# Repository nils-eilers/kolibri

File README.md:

kolibri
=======

About
-----

kolibri is an 8 bit homebrew computer project, based on the 6309 CPU by
Hitachi, a kind of advanced edition of the much more famous CPU 6809 by
Motorola.

kolibri is the german word for colibri aka hummingbird.

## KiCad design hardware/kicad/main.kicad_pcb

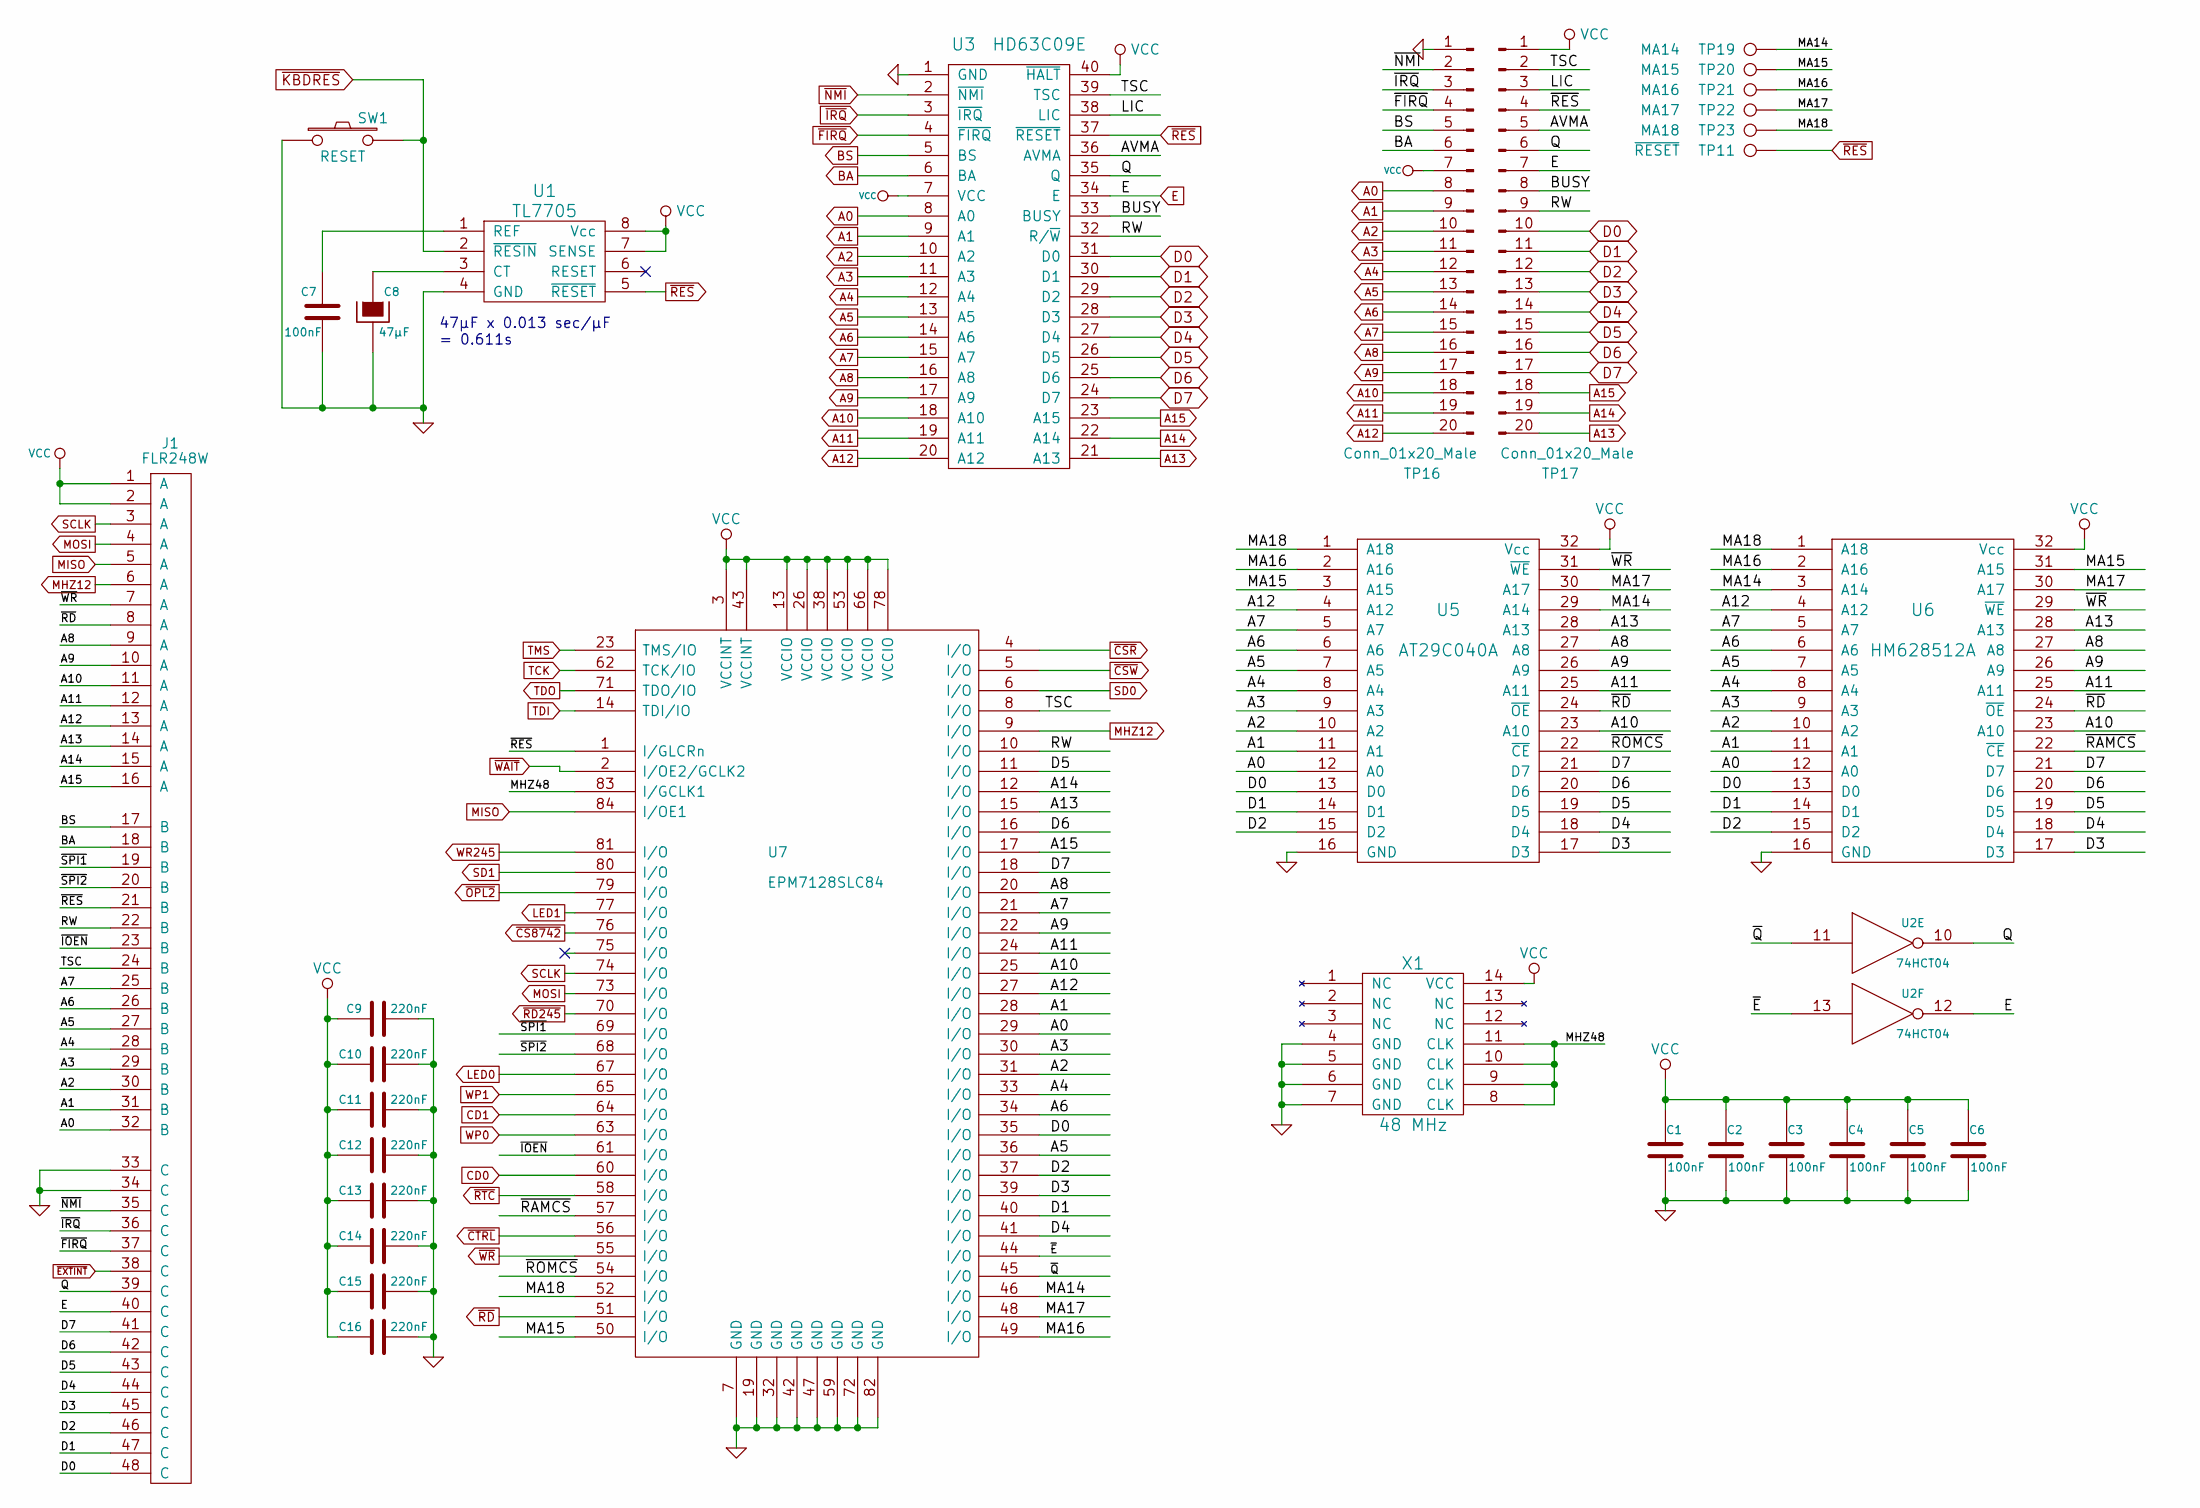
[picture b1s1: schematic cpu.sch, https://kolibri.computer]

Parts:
C1, C2, C3, C4, C5, C6, C7: 100nF; KERKO-5
C8: 47µF; CP-2-5
C9, C10, C11, C12, C13, C14, C15, C16: 220nF; KERKO-5
J1: FLR248W; FL-R2-48W
SW1: RESET; TASTER_3305
TP11: ~RESET; PINTST
TP16, TP17: Conn_01x20_Male; Pin_Header_Straight_1x20_Pitch2.54mm
TP19: MA14; PINTST
TP20: MA15; PINTST
TP21: MA16; PINTST
TP22: MA17; PINTST
TP23: MA18; PINTST
U1: TL7705; DIP-8
U2: 74HCT04; DIP-14
U3: HD63C09E; DIP-40
U5: AT29C040A; DIP-32
U6: HM628512A; DIP-32
U7: EPM7128SLC84; PLCC-84
X1: 48 MHz; OSC

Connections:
/CPU/AVMA: TP17.5, U3.36 (AVMA)
/CPU/BUSY: TP17.8, U3.33 (BUSY)
/CPU/LIC: TP17.3, U3.38 (LIC)
/CPU/MA14: TP19.1, U5.29 (A14), U6.3 (A14), U7.46 (I/O)
/CPU/MA15: TP20.1, U5.3 (A15), U6.31 (A15), U7.50 (I/O)
/CPU/MA16: TP21.1, U5.2 (A16), U6.2 (A16), U7.49 (I/O)
/CPU/MA17: TP22.1, U5.30 (A17), U6.30 (A17), U7.48 (I/O)
/CPU/MA18: TP23.1, U5.1 (A18), U6.1 (A18), U7.52 (I/O)
/CPU/MHZ48: U7.83 (I/GCLK1), X1.8 (CLK), X1.9 (CLK), X1.10 (CLK), X1.11 (CLK)
/CPU/Q: J1.39 (C), TP17.6, U2.10, U3.35 (Q)
/CPU/RW: J1.22 (B), TP17.9, U3.32 (R/~W), U7.10 (I/O)
/CPU/TSC: J1.24 (B), TP17.2, U3.39 (TSC), U7.8 (I/O)
/CPU/~E: U2.13, U7.44 (I/O)
/CPU/~IOEN: J1.23 (B), U7.61 (I/O)
/CPU/~Q: U2.11, U7.45 (I/O)
/CPU/~RAMCS: U6.22 (~CE), U7.57 (I/O)
/CPU/~ROMCS: U5.22 (~CE), U7.54 (I/O)
/CPU/~SPI1: J1.19 (B), U7.69 (I/O)
/CPU/~SPI2: J1.20 (B), U7.68 (I/O)
A0: J1.32 (B), TP16.8, U3.8 (A0), U5.12 (A0), U6.12 (A0), U7.29 (I/O); also elsewhere on the board
A1: J1.31 (B), TP16.9, U3.9 (A1), U5.11 (A1), U6.11 (A1), U7.28 (I/O); also elsewhere on the board
A2: J1.30 (B), TP16.10, U3.10 (A2), U5.10 (A2), U6.10 (A2), U7.31 (I/O); also elsewhere on the board
A3: J1.29 (B), TP16.11, U3.11 (A3), U5.9 (A3), U6.9 (A3), U7.30 (I/O); also elsewhere on the board
A4: J1.28 (B), TP16.12, U3.12 (A4), U5.8 (A4), U6.8 (A4), U7.33 (I/O)
A5: J1.27 (B), TP16.13, U3.13 (A5), U5.7 (A5), U6.7 (A5), U7.36 (I/O)
A6: J1.26 (B), TP16.14, U3.14 (A6), U5.6 (A6), U6.6 (A6), U7.34 (I/O)
A7: J1.25 (B), TP16.15, U3.15 (A7), U5.5 (A7), U6.5 (A7), U7.21 (I/O)
A8: J1.9 (A), TP16.16, U3.16 (A8), U5.27 (A8), U6.27 (A8), U7.20 (I/O)
A9: J1.10 (A), TP16.17, U3.17 (A9), U5.26 (A9), U6.26 (A9), U7.22 (I/O)
A10: J1.11 (A), TP16.18, U3.18 (A10), U5.23 (A10), U6.23 (A10), U7.25 (I/O)
A11: J1.12 (A), TP16.19, U3.19 (A11), U5.25 (A11), U6.25 (A11), U7.24 (I/O)
A12: J1.13 (A), TP16.20, U3.20 (A12), U5.4 (A12), U6.4 (A12), U7.27 (I/O)
A13: J1.14 (A), TP17.20, U3.21 (A13), U5.28 (A13), U6.28 (A13), U7.15 (I/O)
A14: J1.15 (A), TP17.19, U3.22 (A14), U7.12 (I/O)
A15: J1.16 (A), TP17.18, U3.23 (A15), U7.17 (I/O)
BA: J1.18 (B), TP16.6, U3.6 (BA); also elsewhere on the board
BS: J1.17 (B), TP16.5, U3.5 (BS); also elsewhere on the board
CD0: U7.60 (I/O); also elsewhere on the board
CD1: U7.64 (I/O); also elsewhere on the board
D0: J1.48 (C), TP17.10, U3.31 (D0), U5.13 (D0), U6.13 (D0), U7.35 (I/O); also elsewhere on the board
D1: J1.47 (C), TP17.11, U3.30 (D1), U5.14 (D1), U6.14 (D1), U7.40 (I/O); also elsewhere on the board
D2: J1.46 (C), TP17.12, U3.29 (D2), U5.15 (D2), U6.15 (D2), U7.37 (I/O); also elsewhere on the board
D3: J1.45 (C), TP17.13, U3.28 (D3), U5.17 (D3), U6.17 (D3), U7.39 (I/O); also elsewhere on the board
D4: J1.44 (C), TP17.14, U3.27 (D4), U5.18 (D4), U6.18 (D4), U7.41 (I/O); also elsewhere on the board
D5: J1.43 (C), TP17.15, U3.26 (D5), U5.19 (D5), U6.19 (D5), U7.11 (I/O); also elsewhere on the board
D6: J1.42 (C), TP17.16, U3.25 (D6), U5.20 (D6), U6.20 (D6), U7.16 (I/O); also elsewhere on the board
D7: J1.41 (C), TP17.17, U3.24 (D7), U5.21 (D7), U6.21 (D7), U7.18 (I/O); also elsewhere on the board
E: J1.40 (C), TP17.7, U2.12, U3.34 (E); also elsewhere on the board
GND: C1.2, C2.2, C3.2, C4.2, C5.2, C6.2, C7.1, C8.2, C9.2, C10.2, C11.2, C12.2, C13.2, C14.2, C15.2, C16.2, J1.33 (C), J1.34 (C), SW1.1, TP16.1, U1.4 (GND), U2.7 (GND), U3.1 (GND), U5.16 (GND), U6.16 (GND), U7.7 (GND), U7.19 (GND), U7.32 (GND), U7.42 (GND), U7.47 (GND), U7.59 (GND), U7.72 (GND), U7.82 (GND), X1.4 (GND), X1.5 (GND), X1.6 (GND), X1.7 (GND); also elsewhere on the board
LED0: U7.67 (I/O); also elsewhere on the board
LED1: U7.77 (I/O); also elsewhere on the board
MHZ12: J1.6 (A), U7.9 (I/O); also elsewhere on the board
MISO: J1.5 (A), U7.84 (I/OE1); also elsewhere on the board
MOSI: J1.4 (A), U7.73 (I/O); also elsewhere on the board
unnamed: C7.2, U1.1 (REF)
unnamed: C8.1, U1.3 (CT)
SCLK: J1.3 (A), U7.74 (I/O); also elsewhere on the board
SD0: U7.6 (I/O); also elsewhere on the board
SD1: U7.80 (I/O); also elsewhere on the board
TCK: U7.62 (TCK/IO); also elsewhere on the board
TDI: U7.14 (TDI/IO); also elsewhere on the board
TDO: U7.71 (TDO/IO); also elsewhere on the board
TMS: U7.23 (TMS/IO); also elsewhere on the board
VCC: C1.1, C2.1, C3.1, C4.1, C5.1, C6.1, C9.1, C10.1, C11.1, C12.1, C13.1, C14.1, C15.1, C16.1, J1.1 (A), J1.2 (A), TP16.7, TP17.1, U1.7 (SENSE), U1.8 (Vcc), U2.14 (VCC), U3.7 (VCC), U3.40 (~HALT), U5.32 (Vcc), U6.32 (Vcc), U7.3 (VCCINT), U7.13 (VCCIO), U7.26 (VCCIO), U7.38 (VCCIO), U7.43 (VCCINT), U7.53 (VCCIO), U7.66 (VCCIO), U7.78 (VCCIO), X1.14 (VCC); also elsewhere on the board
WP0: U7.63 (I/O); also elsewhere on the board
WP1: U7.65 (I/O); also elsewhere on the board
WR245: U7.81 (I/O); also elsewhere on the board
~CS8742: U7.76 (I/O); also elsewhere on the board
~CSR: U7.4 (I/O); also elsewhere on the board
~CSW: U7.5 (I/O); also elsewhere on the board
~CTRL: U7.56 (I/O); also elsewhere on the board
~EXTINT: J1.38 (C); also elsewhere on the board
~FIRQ: J1.37 (C), TP16.4, U3.4 (~FIRQ); also elsewhere on the board
~IRQ: J1.36 (C), TP16.3, U3.3 (~IRQ); also elsewhere on the board
~KBDRES: SW1.2, U1.2 (~RESIN); also elsewhere on the board
~NMI: J1.35 (C), TP16.2, U3.2 (~NMI); also elsewhere on the board
~OPL2: U7.79 (I/O); also elsewhere on the board
~RD: J1.8 (A), U5.24 (~OE), U6.24 (~OE), U7.51 (I/O); also elsewhere on the board
~RD245: U7.70 (I/O); also elsewhere on the board
~RES: J1.21 (B), TP11.1, TP17.4, U1.5 (~RESET), U3.37 (~RESET), U7.1 (I/GLCRn); also elsewhere on the board
~RTC: U7.58 (I/O); also elsewhere on the board
~WAIT: U7.2 (I/OE2/GCLK2); also elsewhere on the board
~WR: J1.7 (A), U5.31 (~WE), U6.29 (~WE), U7.55 (I/O); also elsewhere on the board

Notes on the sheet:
47µF x 0.013 sec/µF = 0.611s

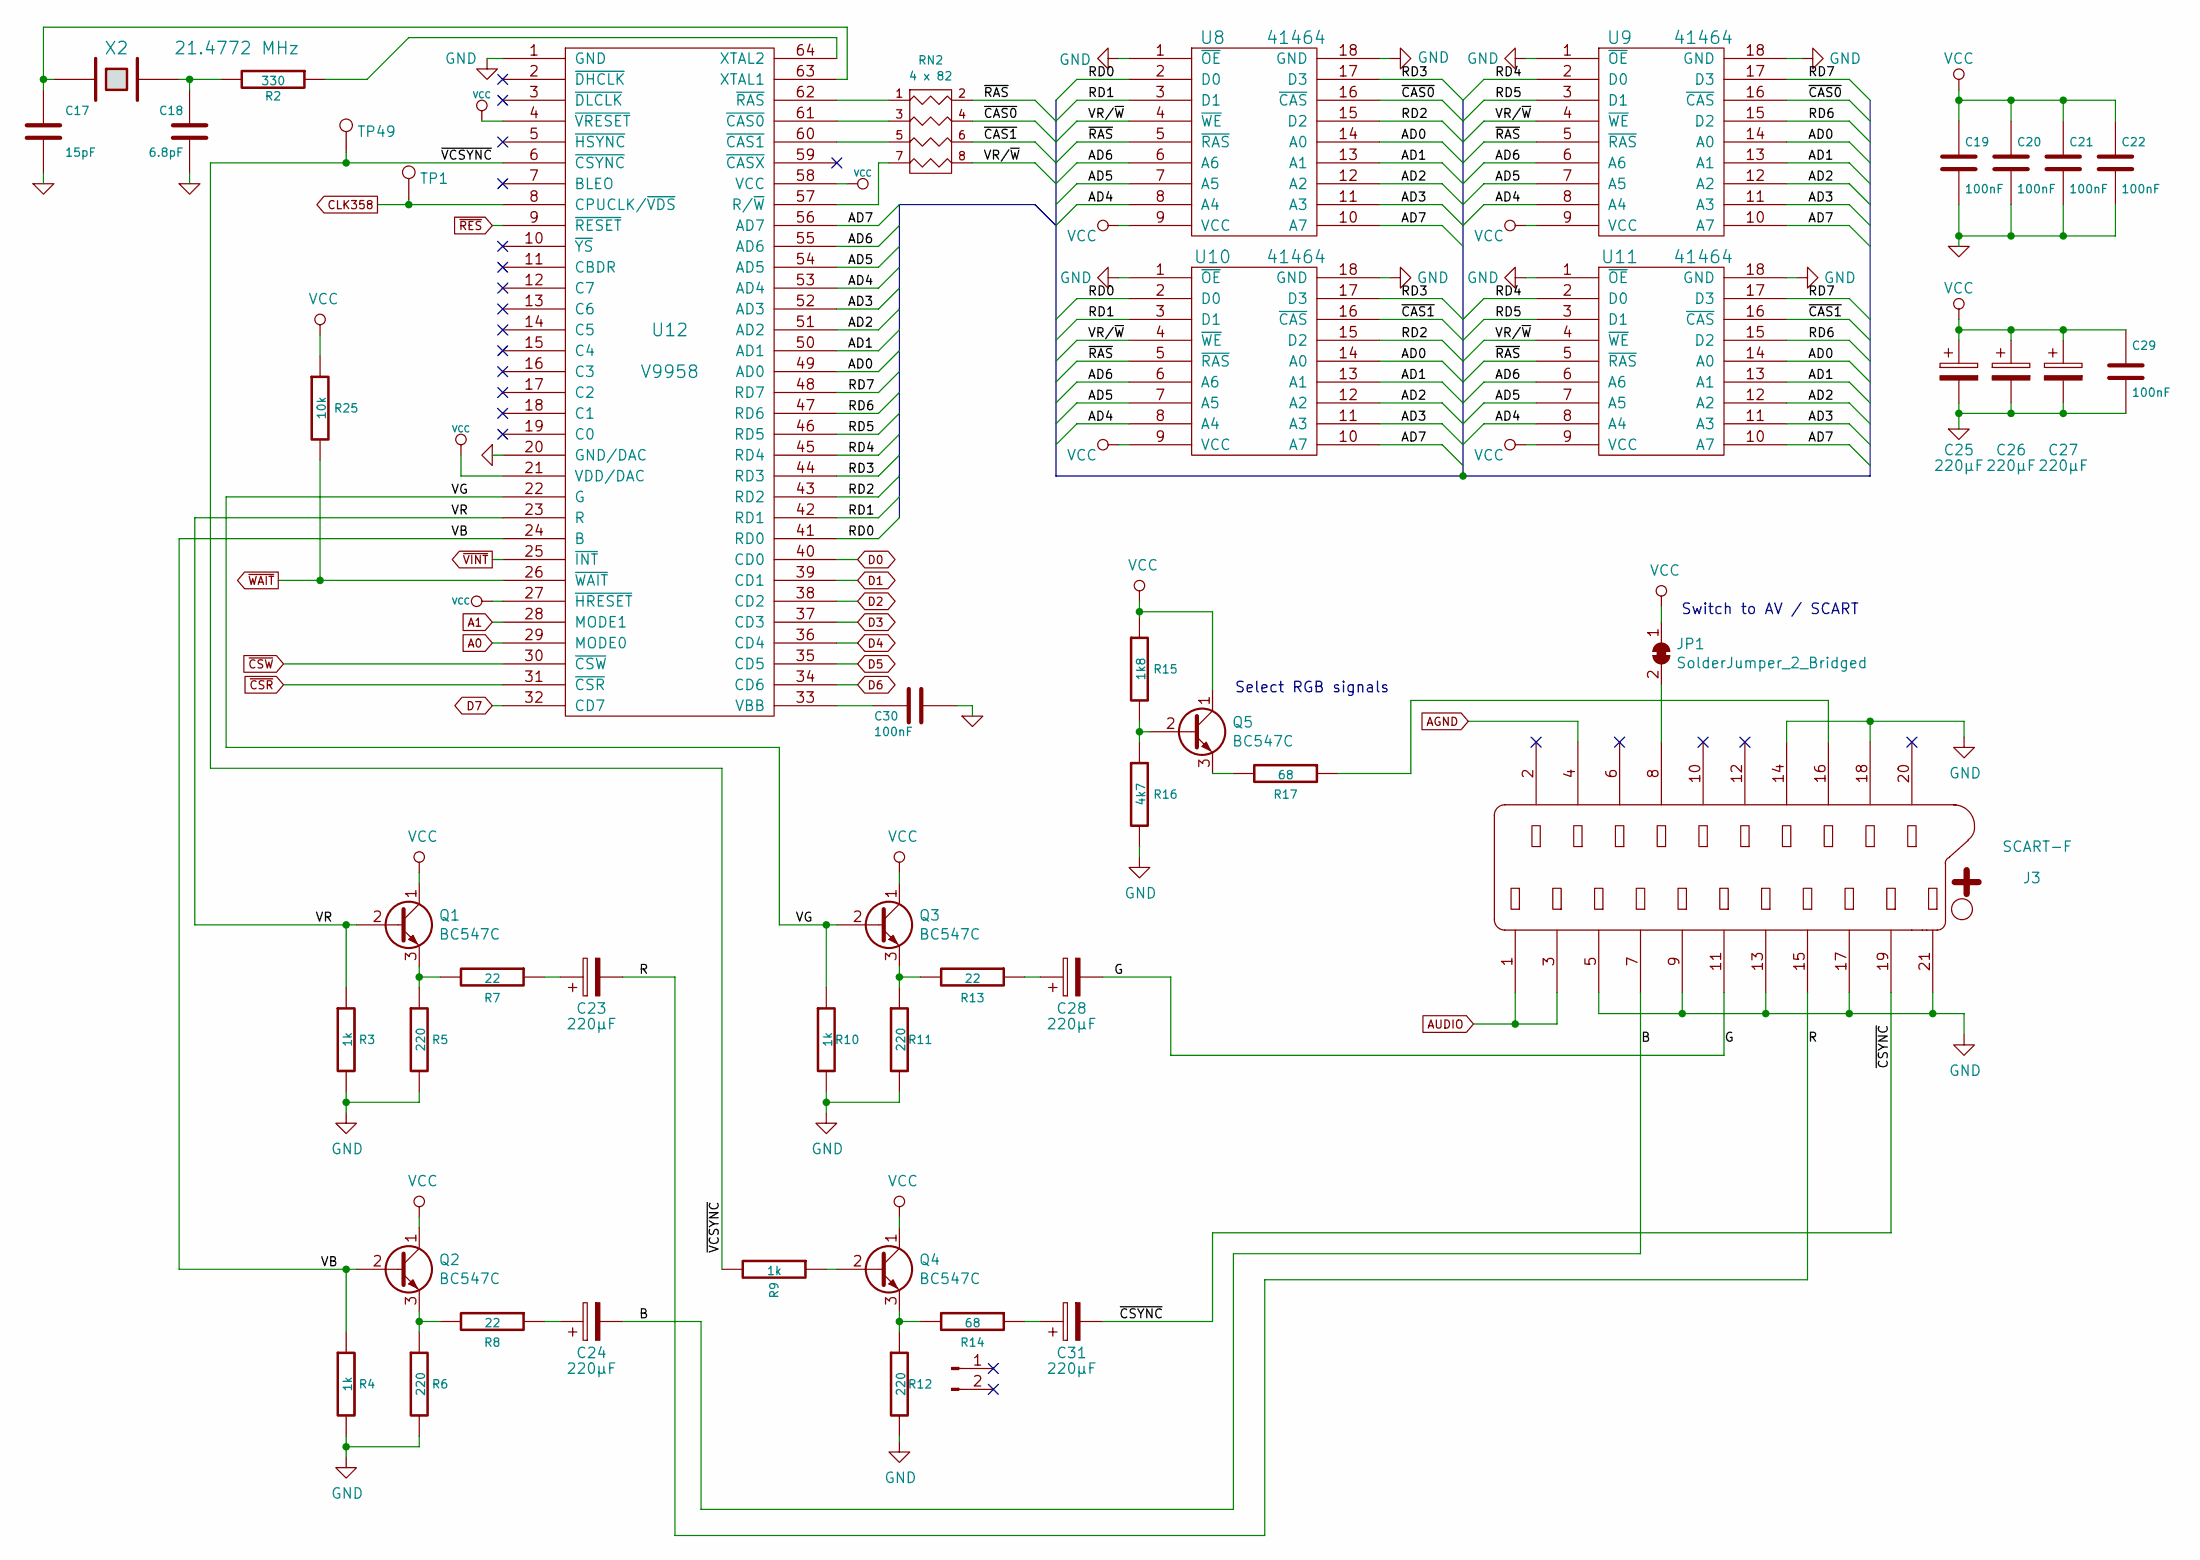
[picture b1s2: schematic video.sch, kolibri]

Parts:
C17: 15pF; KERKO-2
C18: 6.8pF; KERKO-2
C19, C20, C21, C22, C29, C30: 100nF; KERKO-5
C23, C24, C25, C26, C27, C28, C31: 220µF; CP-2-6
J3: SCART-F; SCART
J5: dummy; R_Axial_DIN0204_L3.6mm_D1.6mm_P2.54mm_Vertical
JP1: SolderJumper_2_Bridged; SolderJumper-2_P1.3mm_Bridged_RoundedPad1.0x1.5mm
Q1, Q2, Q3, Q4, Q5: BC547C; TO-92_Inline_Wide
R2: 330; R
R3, R4, R9, R10: 1k; R_Axial_DIN0204_L3.6mm_D1.6mm_P2.54mm_Vertical
R5, R6, R11, R12: 220; R_Axial_DIN0204_L3.6mm_D1.6mm_P2.54mm_Vertical
R7, R8, R13: 22; R_Axial_DIN0204_L3.6mm_D1.6mm_P2.54mm_Vertical
R14, R17: 68; R
R15: 1k8; R
R16: 4k7; R
R25: 10k; R
RN2: 4 x 82; R_Array_SIP8
TP1: CLK358; PINTST
TP49: ~VCSYNC; PINTST
U8, U9, U10, U11: 41464; DIP-18
U12: V9958; SDIL-64
X2: 21.4772 MHz; CRYSTAL-HC49U

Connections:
/Video/AD0: U8.14 (A0), U9.14 (A0), U10.14 (A0), U11.14 (A0), U12.49 (AD0)
/Video/AD1: U8.13 (A1), U9.13 (A1), U10.13 (A1), U11.13 (A1), U12.50 (AD1)
/Video/AD2: U8.12 (A2), U9.12 (A2), U10.12 (A2), U11.12 (A2), U12.51 (AD2)
/Video/AD3: U8.11 (A3), U9.11 (A3), U10.11 (A3), U11.11 (A3), U12.52 (AD3)
/Video/AD4: U8.8 (A4), U9.8 (A4), U10.8 (A4), U11.8 (A4), U12.53 (AD4)
/Video/AD5: U8.7 (A5), U9.7 (A5), U10.7 (A5), U11.7 (A5), U12.54 (AD5)
/Video/AD6: U8.6 (A6), U9.6 (A6), U10.6 (A6), U11.6 (A6), U12.55 (AD6)
/Video/AD7: U8.10 (A7), U9.10 (A7), U10.10 (A7), U11.10 (A7), U12.56 (AD7)
/Video/B: C24.2, J3.7
/Video/G: C28.2, J3.11
/Video/R: C23.2, J3.15
/Video/RD0: U8.2 (D0), U10.2 (D0), U12.41 (RD0)
/Video/RD1: U8.3 (D1), U10.3 (D1), U12.42 (RD1)
/Video/RD2: U8.15 (D2), U10.15 (D2), U12.43 (RD2)
/Video/RD3: U8.17 (D3), U10.17 (D3), U12.44 (RD3)
/Video/RD4: U9.2 (D0), U11.2 (D0), U12.45 (RD4)
/Video/RD5: U9.3 (D1), U11.3 (D1), U12.46 (RD5)
/Video/RD6: U9.15 (D2), U11.15 (D2), U12.47 (RD6)
/Video/RD7: U9.17 (D3), U11.17 (D3), U12.48 (RD7)
/Video/VB: Q2.2 (B), R4.1, U12.24 (B)
/Video/VG: Q3.2 (B), R10.1, U12.22 (G)
/Video/VR: Q1.2 (B), R3.1, U12.23 (R)
/Video/VR/~W: RN2.8 (R4), U8.4 (~WE), U9.4 (~WE), U10.4 (~WE), U11.4 (~WE)
/Video/~CAS0: RN2.4 (R2), U8.16 (~CAS), U9.16 (~CAS)
/Video/~CAS1: RN2.6 (R3), U10.16 (~CAS), U11.16 (~CAS)
/Video/~CSYNC: C31.2, J3.19
/Video/~RAS: RN2.2 (R1), U8.5 (~RAS), U9.5 (~RAS), U10.5 (~RAS), U11.5 (~RAS)
/Video/~VCSYNC: R9.2, TP49.1, U12.6 (~CSYNC)
A0: U12.29 (MODE0); also elsewhere on the board
A1: U12.28 (MODE1); also elsewhere on the board
AGND: J3.4; also elsewhere on the board
AUDIO: J3.1, J3.3; also elsewhere on the board
CLK358: TP1.1, U12.8 (CPUCLK/~VDS); also elsewhere on the board
D0: U12.40 (CD0); also elsewhere on the board
D1: U12.39 (CD1); also elsewhere on the board
D2: U12.38 (CD2); also elsewhere on the board
D3: U12.37 (CD3); also elsewhere on the board
D4: U12.36 (CD4); also elsewhere on the board
D5: U12.35 (CD5); also elsewhere on the board
D6: U12.34 (CD6); also elsewhere on the board
D7: U12.32 (CD7); also elsewhere on the board
GND: C17.2, C18.2, C19.2, C20.2, C21.2, C22.2, C25.2, C26.2, C27.2, C29.2, C30.1, J3.5, J3.9, J3.13, J3.14, J3.17, J3.18, J3.21, R3.2, R4.2, R5.2, R6.2, R10.2, R11.2, R12.2, R16.2, U8.1 (~OE), U8.18 (GND), U9.1 (~OE), U9.18 (GND), U10.1 (~OE), U10.18 (GND), U11.1 (~OE), U11.18 (GND), U12.1 (GND), U12.20 (GND/DAC); also elsewhere on the board
unnamed: C17.1, U12.63 (XTAL1), X2.1
unnamed: C18.1, R2.2, X2.2
unnamed: C23.1, R7.1
unnamed: C24.1, R8.1
unnamed: C28.1, R13.1
unnamed: C30.2, U12.33 (VBB)
unnamed: C31.1, R14.1
unnamed: J3.8, JP1.2 (B)
unnamed: J3.16, R17.1
unnamed: Q1.3 (E), R5.1, R7.2
unnamed: Q2.3 (E), R6.1, R8.2
unnamed: Q3.3 (E), R11.1, R13.2
unnamed: Q4.2 (B), R9.1
unnamed: Q4.3 (E), R12.1, R14.2
unnamed: Q5.2 (B), R15.2, R16.1
unnamed: Q5.3 (E), R17.2
unnamed: R2.1, U12.64 (XTAL2)
unnamed: RN2.1, U12.62 (~RAS)
unnamed: RN2.3, U12.61 (~CAS0)
unnamed: RN2.5, U12.60 (~CAS1)
unnamed: RN2.7, U12.57 (R/~W)
VCC: C19.1, C20.1, C21.1, C22.1, C25.1, C26.1, C27.1, C29.1, JP1.1 (A), Q1.1 (C), Q2.1 (C), Q3.1 (C), Q4.1 (C), Q5.1 (C), R15.1, R25.1, U8.9 (VCC), U9.9 (VCC), U10.9 (VCC), U11.9 (VCC), U12.4 (~VRESET), U12.21 (VDD/DAC), U12.27 (~HRESET), U12.58 (VCC); also elsewhere on the board
~CSR: U12.31 (~CSR); also elsewhere on the board
~CSW: U12.30 (~CSW); also elsewhere on the board
~RES: U12.9 (~RESET); also elsewhere on the board
~VINT: U12.25 (~INT); also elsewhere on the board
~WAIT: R25.2, U12.26 (~WAIT); also elsewhere on the board

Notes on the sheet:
Select RGB signals
Switch to AV / SCART

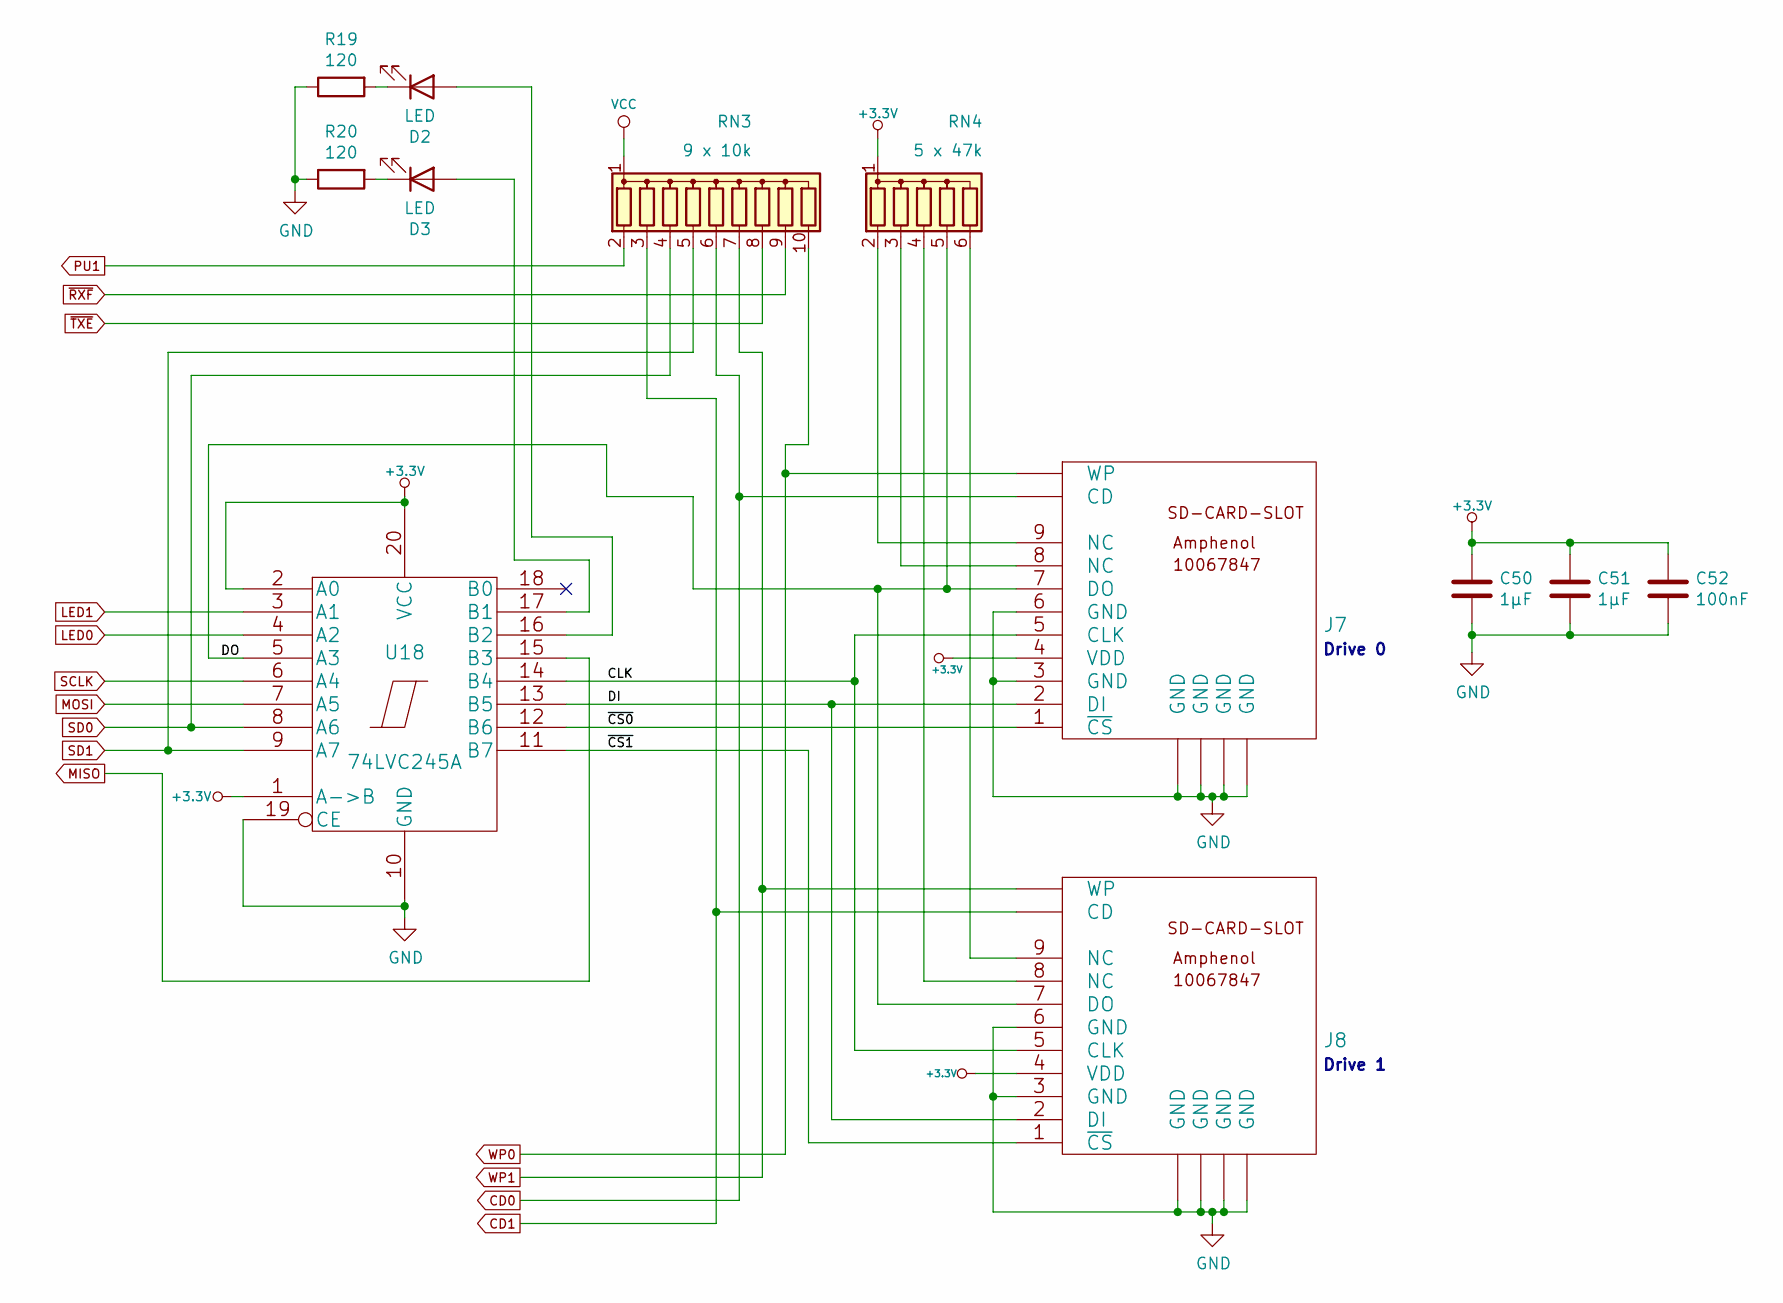
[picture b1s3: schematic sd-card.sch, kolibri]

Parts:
C50, C51: 1µF; KERKO-5
C52: 100nF; KERKO-5
D2, D3: LED; LED-RND-135-00093
J7, J8: 10067847; SD-SOCKET
R19, R20: 120; R
RN3: 9 x 10k; R_Array_SIP10
RN4: 5 x 47k; R_Array_SIP6
U18: 74LVC245A; DIP-20

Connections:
+3.3V: C50.1, C51.1, C52.1, J7.4 (VDD), J8.4 (VDD), RN4.1 (common), U18.1 (A->B), U18.2 (A0), U18.20 (VCC); also elsewhere on the board
/SD Card/CLK: J7.5 (CLK), J8.5 (CLK), U18.14 (B4)
/SD Card/DI: J7.2 (DI), J8.2 (DI), U18.13 (B5)
/SD Card/DO: J7.7 (DO), J8.7 (DO), RN4.5 (R4), U18.5 (A3)
/SD Card/~CS0: J7.1 (~CS), U18.12 (B6)
/SD Card/~CS1: J8.1 (~CS), U18.11 (B7)
CD0: J7.CD, RN3.6 (R5); also elsewhere on the board
CD1: J8.CD, RN3.3 (R2); also elsewhere on the board
GND: C50.2, C51.2, C52.2, J7.3 (GND), J7.6 (GND), J7.GND1 (GND), J7.GND2 (GND), J7.GND3 (GND), J7.GND4 (GND), J8.3 (GND), J8.6 (GND), J8.GND1 (GND), J8.GND2 (GND), J8.GND3 (GND), J8.GND4 (GND), R19.1, R20.1, U18.10 (GND), U18.19 (CE); also elsewhere on the board
LED0: U18.4 (A2); also elsewhere on the board
LED1: U18.3 (A1); also elsewhere on the board
MISO: U18.15 (B3); also elsewhere on the board
MOSI: U18.7 (A5); also elsewhere on the board
unnamed: D2.1 (K), R19.2
unnamed: D2.2 (A), U18.16 (B2)
unnamed: D3.1 (K), R20.2
unnamed: D3.2 (A), U18.17 (B1)
unnamed: J7.8 (NC), RN4.3 (R2)
unnamed: J7.9 (NC), RN4.2 (R1)
unnamed: J8.8 (NC), RN4.4 (R3)
unnamed: J8.9 (NC), RN4.6 (R5)
PU1: RN3.2 (R1); also elsewhere on the board
SCLK: U18.6 (A4); also elsewhere on the board
SD0: RN3.4 (R3), U18.8 (A6); also elsewhere on the board
SD1: RN3.5 (R4), U18.9 (A7); also elsewhere on the board
VCC: RN3.1 (common); also elsewhere on the board
WP0: J7.WP, RN3.10 (R9); also elsewhere on the board
WP1: J8.WP, RN3.7 (R6); also elsewhere on the board
~RXF: RN3.9 (R8); also elsewhere on the board
~TXE: RN3.8 (R7); also elsewhere on the board

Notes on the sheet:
Drive 0
Drive 1

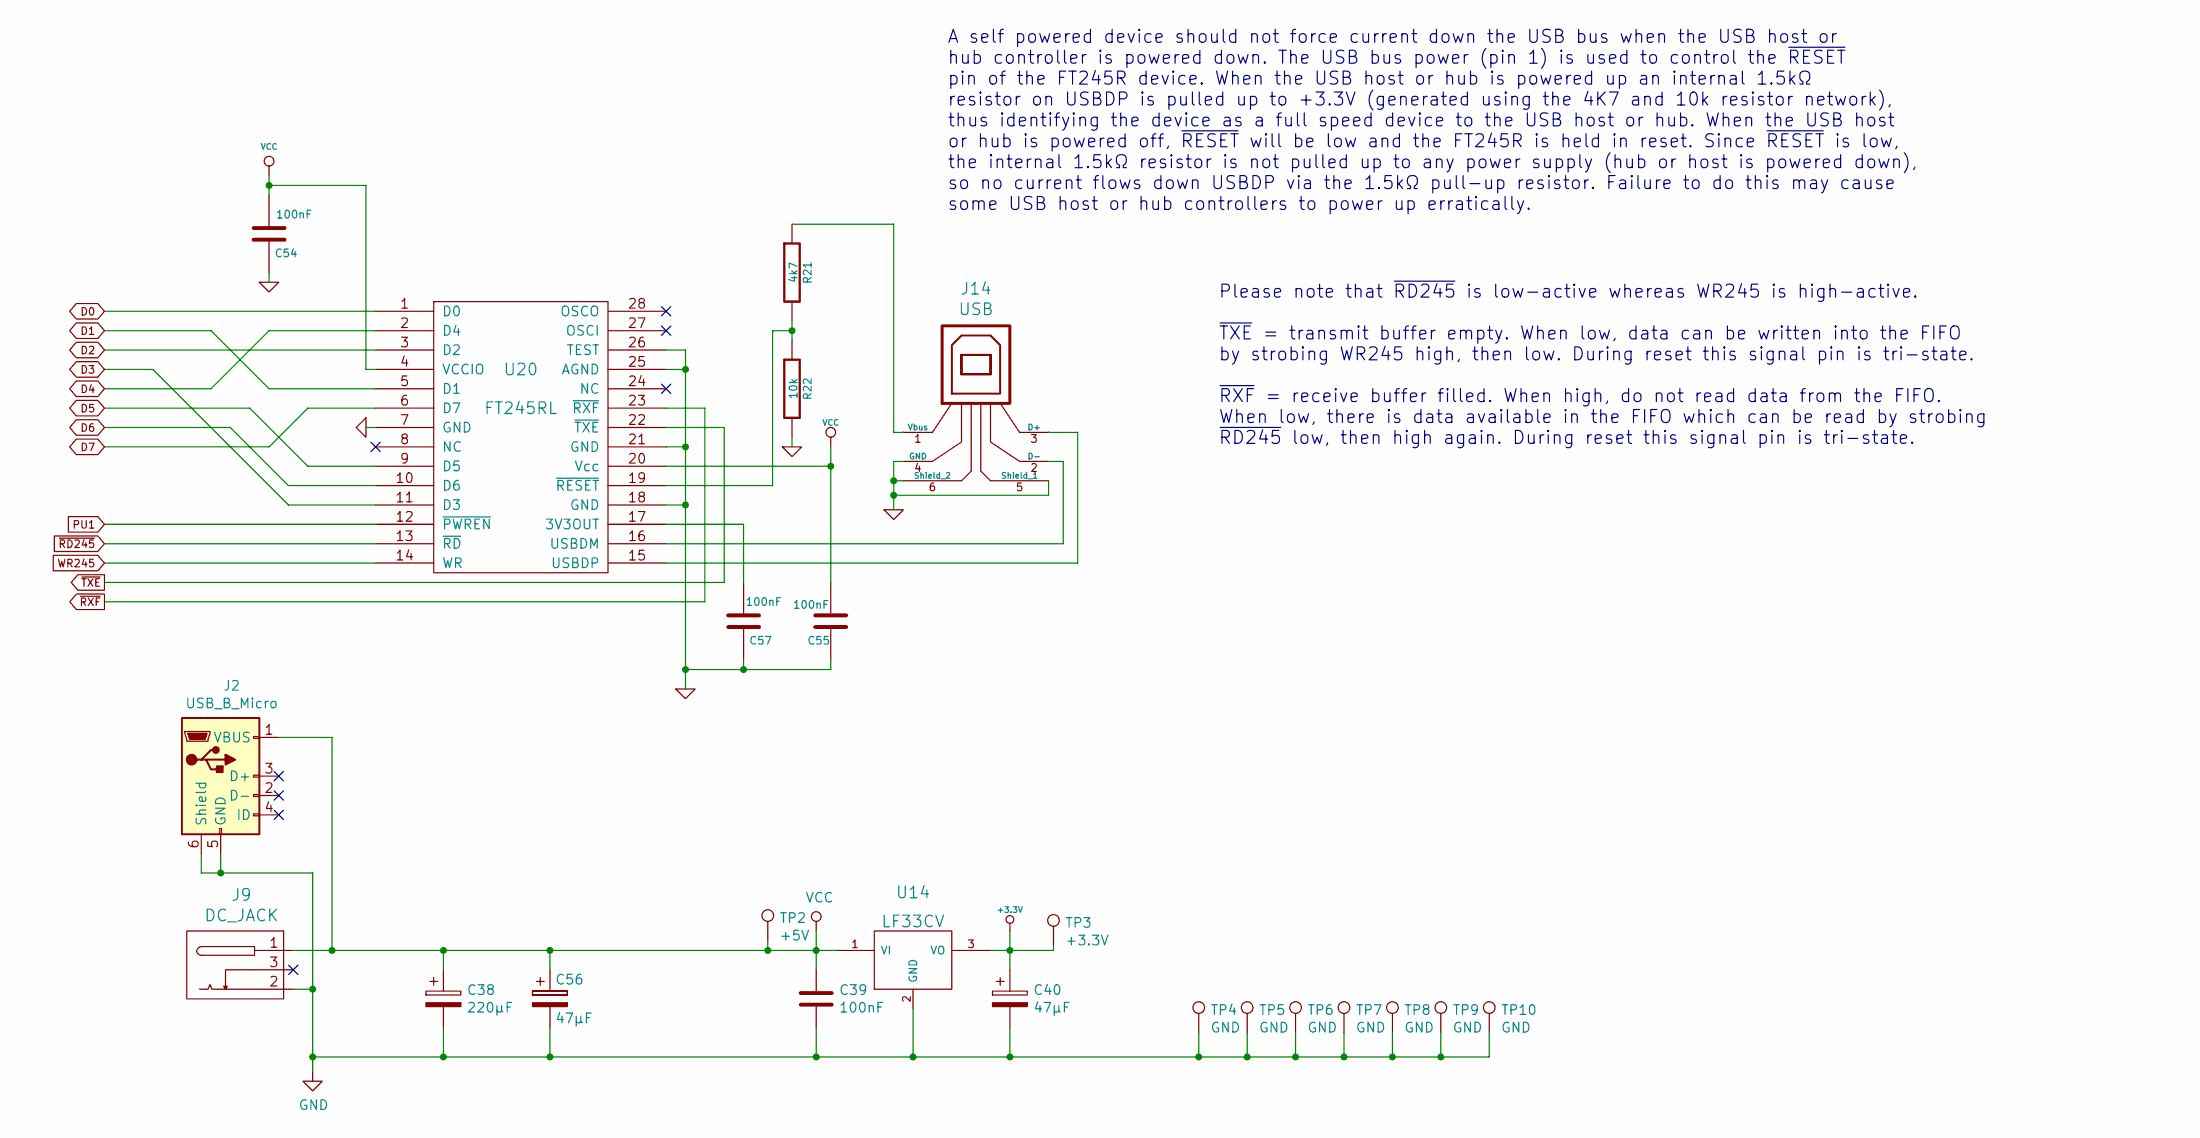
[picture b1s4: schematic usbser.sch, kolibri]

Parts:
C38: 220µF; CP-2-6
C39, C54, C55, C57: 100nF; KERKO-5
C40, C56: 47µF; CP-2-5
J2: USB_B_Micro; micro-usb-amphenol-10103594
J9: DC_JACK; JACK_ALIM
J14: USB; USB_B
R21: 4k7; R
R22: 10k; R
TP2: +5V; PINTST
TP3: +3.3V; PINTST
TP4, TP5, TP6, TP7, TP8, TP9, TP10: GND; PINTST
U14: LF33CV; TO-220-HORIZ
U20: FT245RL; SSOP-28

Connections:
+3.3V: C40.1, TP3.1, U14.3 (VO); also elsewhere on the board
D0: U20.1 (D0); also elsewhere on the board
D1: U20.5 (D1); also elsewhere on the board
D2: U20.3 (D2); also elsewhere on the board
D3: U20.11 (D3); also elsewhere on the board
D4: U20.2 (D4); also elsewhere on the board
D5: U20.9 (D5); also elsewhere on the board
D6: U20.10 (D6); also elsewhere on the board
D7: U20.6 (D7); also elsewhere on the board
GND: C38.2, C39.2, C40.2, C54.1, C55.1, C56.2, C57.1, J2.5 (GND), J2.6 (Shield), J9.2, J14.4 (GND), J14.5 (Shield_1), J14.6 (Shield_2), R22.2, TP4.1, TP5.1, TP6.1, TP7.1, TP8.1, TP9.1, TP10.1, U14.2 (GND), U20.7 (GND), U20.18 (GND), U20.21 (GND), U20.25 (AGND), U20.26 (TEST); also elsewhere on the board
unnamed: C57.2, U20.17 (3V3OUT)
unnamed: J14.1 (Vbus), R21.1
unnamed: J14.2 (D-), U20.16 (USBDM)
unnamed: J14.3 (D+), U20.15 (USBDP)
unnamed: R21.2, R22.1, U20.19 (~RESET)
PU1: U20.12 (~PWREN); also elsewhere on the board
VCC: C38.1, C39.1, C54.2, C55.2, C56.1, J2.1 (VBUS), J9.1, TP2.1, U14.1 (VI), U20.4 (VCCIO), U20.20 (Vcc); also elsewhere on the board
WR245: U20.14 (WR); also elsewhere on the board
~RD245: U20.13 (~RD); also elsewhere on the board
~RXF: U20.23 (~RXF); also elsewhere on the board
~TXE: U20.22 (~TXE); also elsewhere on the board

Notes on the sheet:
Please note that ~RD245~ is low-active whereas WR245 is high-active. ~TXE~ = transmit buffer empty. When low, data can be written into the FIFO by strobing WR245 high, then low. During reset this signal pin is tri-state. ~RXF~ = receive buffer filled. When high, do not read data from the FIFO. When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
A self powered device should not force current down the USB bus when the USB host or hub controller is powered down. The USB bus power (pin 1) is used to control the ~RESET~ pin of the FT245R device. When the USB host or hub is powered up an internal 1.5kΩ resistor on USBDP is pulled up to +3.3V (g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
